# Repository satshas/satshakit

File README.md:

**IMPORTANT:** this repository is outdated, please find all the new repos about the satshakit boards here: **[satshakit Github organization](https://github.com/satshakit/)**

<h1 style="font-family: courier;" align="center"> satshakit</h1>
<p align="center">

<div align="center"><i>An improved & fabbable 100% Arduino IDE/libraries compatible board.</i></div>
</p>  

The story
--
satshakit born during my **[FabAcademy2015](http://fabacademy.org/archives/2015/eu/students/ingrassia.daniele/index.html)**  as one the first test boards for my quadcopter final project. As some of my fellow students had difficulties with **[Fabkit](http://fabacademy.org/archives/2015/doc/projects/fabkit-0.4.html)**, they tried to make this prototype board. The board was very appreciated that now almost all my fellow students made it for their exercises, or use it as a **starting point for their final projects**. Thus I decided to do this release, if anyone wants to try it. Now, one year later, I am again in a FabLab developing new satshakit boards in my spare time.

What is satshakit?
--

satshakit is a **100% Arduino IDE  and libraries compatible**, fabbable and open source board, and also an improved version of [Fabkit](http://fabacademy.org/archives/2015/doc/projects/fabkit-0.4.html). 

Main **improvements and features** over Fabkit are:

- **16Mhz** instead of 8Mhz
- **crystal** instead of resonator
- **costs less** (7-9 euro vs 13 euro)
- 100% compatible with **default Arduino IDE** (satshakit is recognized as Arduino UNO)
- ADC6/7 connected instead of ADC6/7 not connected (satshakit laser and cnc)
- larger space to easy soldering (satshakit laser and cnc)

satshakit boards
--

There are different kinds of **satshakit boards** depending on the **fabrication technique** you will use to make them, or on the **size** of the board. 

Here is a comparison table about different satshakit boards:

|name|mcu|pins|size(mm)|
| :---: | :---:|:---:|:---:|
|`satshakit laser`|ATmega328P|Arduino + ADC6/7|48 x 42|
|`satshakit cnc`|ATmega328P| Arduino + ADC6/7  |54 x 45|
|`satshakit multicore`|2 x ATmega328P| 2 x Arduino + ADC6/7|50 x 42|
|`satshakit micro`| ATmega328P|Arduino|40 x 24|

satshakit laser and cnc
--

**satshakit laser** and **satshakit cnc** are the standard versions of the satshakit. They are actually the same board, showing some layout differences to improve the fabrication process using a **fiber laser** cutter machine, or a little **cnc mill**. These satshakits are meant to be a general purpose board, having the full Arduino pinout plus ADC6/7 pins, large space for easy soldering and two led onboard for power and pin 13.

Here is the **satshakit laser board**:

And this is the **satshakit cnc board**:

**downloads (right click, download as)**

- [satshakit cnc svg](https://raw.githubusercontent.com/satshas/satshakit/master/media/satshakit_cnc/satshakit_cnc.svg)
- [satshakit cnc internal png](https://raw.githubusercontent.com/satshas/satshakit/master/media/satshakit_cnc/satshakit_cnc_internal.png)
- [satshakit cnc holes png](https://raw.githubusercontent.com/satshas/satshakit/master/media/satshakit_cnc/satshakit_cnc_holes.png)
- [satshakit cnc cut png](https://raw.githubusercontent.com/satshas/satshakit/master/media/satshakit_cnc/satshakit_cnc_cut.png)
- [satshakit cnc cut tips png](https://raw.githubusercontent.com/satshas/satshakit/master/media/satshakit_cnc/satshakit_cnc_cut_tip.png)
- [satshakit cnc schematic](https://raw.githubusercontent.com/satshas/satshakit/master/eagle_projects/satshakit_cnc/satshakit_cnc.sch)
- [satshakit cnc board](https://raw.githubusercontent.com/satshas/satshakit/master/eagle_projects/satshakit_cnc/satshakit_cnc.brd)
- [satshakit laser svg](https://raw.githubusercontent.com/satshas/satshakit/master/media/satshakit_laser/satshakit_laser.svg)
- [satshakit laser schematic](https://raw.githubusercontent.com/satshas/satshakit/master/eagle_projects/satshakit_laser/satshakit_laser.sch)
- [satshakit laser board](https://raw.githubusercontent.com/satshas/satshakit/master/eagle_projects/satshakit_laser/satshakit_laser.brd)
- [satshakit laser and cnc BOM Open Document](https://github.com/satshas/satshakit/raw/master/docs/satshakit_others/satshakit_BOM.ods)
- [satshakit laser and cnc BOM Excel](https://github.com/satshas/satshakit/raw/master/docs/satshakit_others/satshakit_BOM.xlsx)

**media**

satshakit laser:

satshakit cnc:

satshakit cnc blinks:

satshakit programmed with a FabISP:

Here are some videos of satshakit while is working with **different configuration and/or sensors**:

satshakit car with sonars sensors and Raspberry Pi:

satshakit little radar, a **satshakit modified board** with an ULN2003A:

satshakit micro
--

**satshakit micro** is a downsized version of the satshakit laser and cnc, developed to be used in **constrained space applications** like embedding the board in textiles or in small objects, or useful for who wants just a **bare metal board** to start with, also easy to be modified and/or customized. While satshakit micro is less than half the size of the other satshakits, it's a **full featured board** with the full Adruino pinout, missing only the possibility to be programmed using an FTDI cable.

Here is the **satshakit micro board**:

**downloads (right click, download as)**

- [satshakit micro svg](https://raw.githubusercontent.com/satshas/satshakit/master/media/satshakit_micro/satshakit_micro.svg)
- [satshakit micro internal png](https://raw.githubusercontent.com/satshas/satshakit/master/media/satshakit_micro/satshakit_micro_internal.png)
- [satshakit micro holes png](https://raw.githubusercontent.com/satshas/satshakit/master/media/satshakit_micro/satshakit_micro_holes.png)
- [satshakit micro cut png](https://raw.githubusercontent.com/satshas/satshakit/master/media/satshakit_micro/satshakit_micro_cut.png)
- [satshakit micro cut tips png](https://raw.githubusercontent.com/satshas/satshakit/master/media/satshakit_micro/satshakit_micro_cut_tips.png)
- [satshakit micro schematic](https://raw.githubusercontent.com/satshas/satshakit/master/eagle_projects/satshakit_micro/satshakit_micro.sch)
- [satshakit micro board](https://raw.githubusercontent.com/satshas/satshakit/master/eagle_projects/satshakit_micro/satshakit_micro.brd)
- [satshakit micro BOM Open Document](https://github.com/satshas/satshakit/raw/master/docs/satshakit_micro/satshakit_micro_BOM.ods)
- [satshakit micro BOM Excel](https://github.com/satshas/satshakit/raw/master/docs/satshakit_micro/satshakit_micro_BOM.xlsx)

**media**

satshakit micro blink:

satshakit multicore
--

**satshakit multicore** boards born as a further experiment on **MCU multithreading and networking**. satshakit multicore boards have only the following modifications in confront of the standard satshakit: 4 extra pin headers (1 GND,1 VCC,1 A4, 1 A5). These pin headers serve also a structural pillars to build a modular satshakit tower. So modular satshakit share the same power source, and can direct communicate with **I2C**. 

Here is the **satshakit multicore board**:

**downloads (right click, download as)**

- [satshakit multicore svg](https://raw.githubusercontent.com/satshas/satshakit/master/media/satshakit_multicore/satshakit_multicore.svg)
- [satshakit multicore schematic](https://raw.githubusercontent.com/satshas/satshakit/master/eagle_projects/satshakit_multicore/satshakit_multicore.sch)
- [satshakit multicore board](https://raw.githubusercontent.com/satshas/satshakit/master/eagle_projects/satshakit_multicore/satshakit_multicore.brd)
- [satshakit multicore BOM Open Document](https://github.com/satshas/satshakit/raw/master/docs/satshakit_others/satshakit_BOM.ods)
- [satshakit multicore BOM Excel](https://github.com/satshas/satshakit/raw/master/docs/satshakit_others/satshakit_BOM.xlsx)

**media**

5-core satshakit system:

satshakit multicore assembly & test:

satshakit multicore blink:

quad satshakit bluetooth triangulation:

satshakit power board
--

Due to the power requirements of a multicore satshakit system and to eventually provide power to **3.3V devices**, I have also developed a simple power board. This power board can work with 7V-12V as input voltage, and give out 5V and 3.3V. I made this power board with the components I had available, obviously you can make this board only with SMD components.

**downloads (right click, download as)**

- [satshakit power board schematic](https://raw.githubusercontent.com/satshas/satshakit/master/eagle_projects/satshakit_power_board/satshakit_power_board.sch)
- [satshakit power board board](https://raw.githubusercontent.com/satshas/satshakit/master/eagle_projects/satshakit_power_board/satshakit_power_board.brd)

Here is a picture of a soldered power board:

Getting Started
--
A satshakit board is **totally like an Arduino board**, thus is possible to use the Arduino IDE without any modification. When you finish solder satshakit, you're ready to program it. If you want to use satshakit as an Arduino, you first need to **upload Arduino bootloader**. This will also set the ATmega328P fuses as the same of an Arduino UNO.
 To do this you need to use a **programmer**, for example another Arduino or FabISP. If you plan to program a satshakit with an Arduino, be sure to upload the **Arduino as ISP skecth** before connecting the satshakit to it.

Here are the connection schemas to program **satshakit laser**, **satshakit cnc** or a **satshakit multicore** with an Arduino as ISP or with a FabISP:

If you made a **satshakit micro**, here are the connection schemas to program it as before for the other satshakits:

Once everything is connected, follow these steps to upload Arduino bootloader:

1. open Arduino IDE 
2. select proper programmer (for example Arduino as ISP or USBtinyISP) 
3. select Arduino UNO as board
4. click on tools->Burn Bootloader

If you made a satshakit cnc, satshakit laser or satshakit multicore, you can use an **FTDI USB cable to upload and use you favourite sketch** without the need to use a programmer anymore. If you made a satshakit micro, you have always to use a programmer, and use the **Sketch >Upload using a programmer** function of the Arduino IDE.

Here is the connection schema to program a satshakit using the FTDI cable:

Remember that if you don't have an FTDI cable you always need a programmer, and to select **File->Upload using a programmer** to upload the code to satshakit.

To use a satshakit like an Arduino, here is the Arduino pinout on satshakit cnc, satshakit laser and satshakit multicore:

And here is the Arduino pinout of the satshakit micro:

What's in the repo
--
- **[docs](https://github.com/satshas/satshakit/tree/master/docs)**: BOM files for Farnell
- **[egle projects](https://github.com/satshas/satshakit/tree/master/eagle_projects)**: eagle projects of satshakit
- **[media](https://github.com/satshas/satshakit/tree/master/media)**: svg of satshakits, connections schemas, images for cnc milling machine and fiber laser cutter, other images

Authors
--

**satshakit cnc and micro:**
- Daniele Ingrassia

**satshakit laser, multicore and power board:**

- Daniele Ingrassia and [Engineering Ingegneria Informatica](http://www.eng.it)

Contact
--
- **ingrassiada@gmail.com**
- **[linkedin](http://it.linkedin.com/in/danieleingrassia)**

Thanks
--
[Fablab opendot](http://www.opendotlab.it/)<br />
info@opendotlab.it<br />
Via Tertulliano N70, 20137, Milan, Italy<br />
 +39.02.36519890<br />

[Fablab Kamp-Lintfort](http://fablab.hochschule-rhein-waal.de/index.php/de/)<br />
Hochschule Rhein-Waal<br />
Friedrich-Heinrich-Allee 25, 47475 Kamp-Lintfort, Germany<br />
fablab@hochschule-rhein-waal.de

License
--
This work is licensed under the terms of Attribution-ShareAlike 4.0 International ([CC BY-NC-SA 4.0](https://creativecommons.org/licenses/by-sa/4.0/)).

Disclaimer  
--

<div class="align-justify">
This hardware/software is provided "as is", and you use the hardware/software at your own risk. Under no circumstances shall any author be liable for direct, indirect, special, incidental, or consequential damages resulting from the use, misuse, or inability to use this hardware/software, even if the authors have been advised of the possibility of such damages.</div>

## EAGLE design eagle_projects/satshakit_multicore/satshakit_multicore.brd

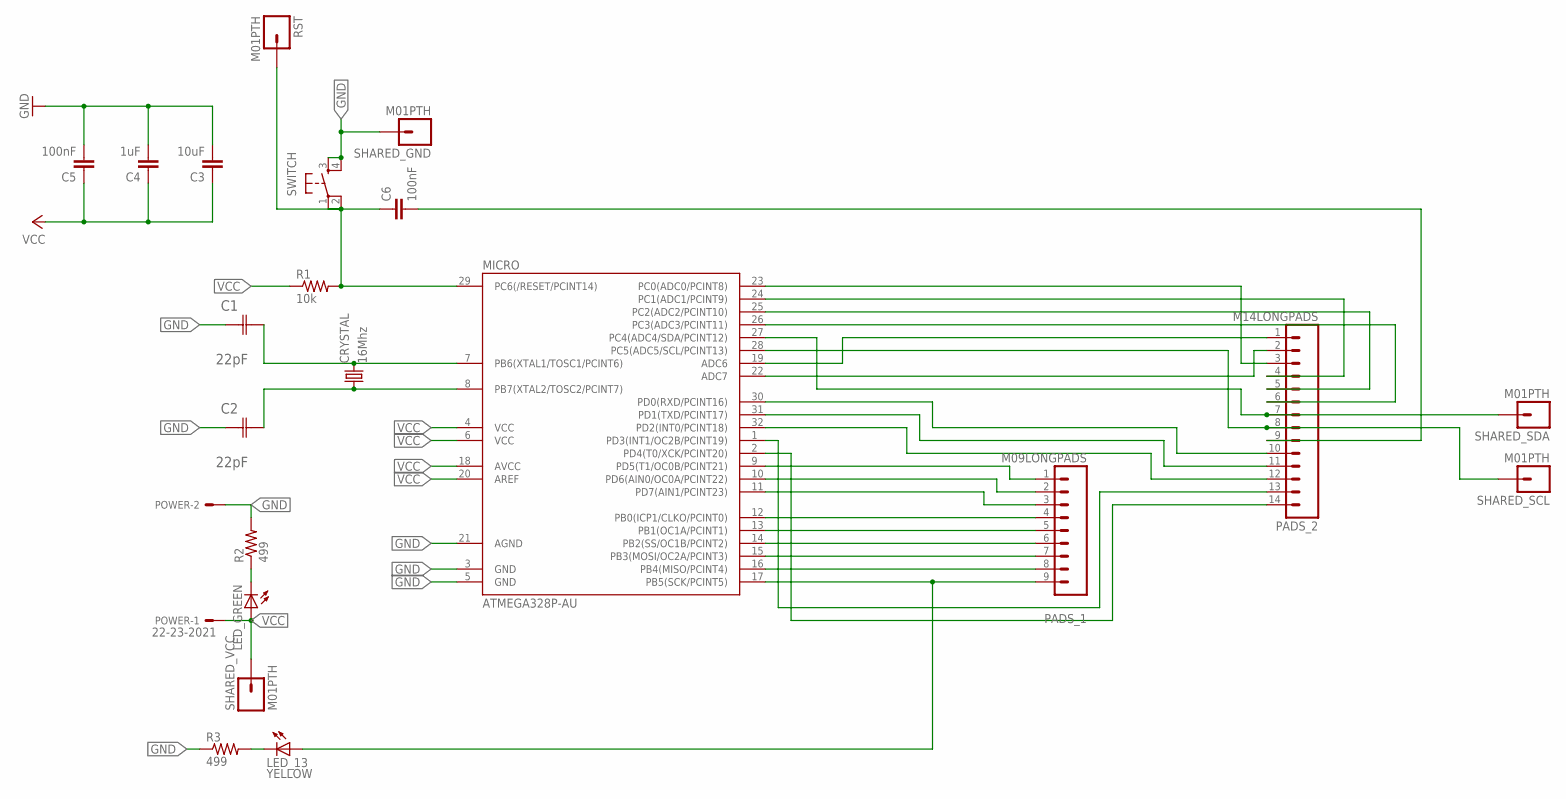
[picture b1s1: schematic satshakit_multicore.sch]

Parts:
C1, C2: 22pF; CAPC3216X178N
C3: 10uF; 1206
C4: 1uF; 1206
C5, C6: 100nF; 1206
CRYSTAL: 16Mhz; CSM-7X-DU
LED_13: YELLOW; 1206
LED_GREEN: LED1206; 1206
MICRO: ATMEGA328P-AU; TQFP32-08
PADS_1: M09LONGPADS; 1X09_LONGPADS
PADS_2: M14LONGPADS; 1X14-LONGPADS
POWER: 22-23-2021
R1: 10k; 1206
R2, R3: 499; 1206
RST: M01PTH; 1X01
SHARED_GND: M01PTH; 1X01
SHARED_SCL: M01PTH; 1X01
SHARED_SDA: M01PTH; 1X01
SHARED_VCC: M01PTH; 1X01
SWITCH: 6MM_SWITCH6MM_SWITCH; 6MM_SWITCH

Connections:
GND: C1.1 (C1), C2.1 (C1), C3.2, C4.2, C5.2, MICRO.3 (GND), MICRO.5 (GND), MICRO.21 (AGND), POWER.2, R2.2, R3.1, SHARED_GND.1, SWITCH.3 (S), SWITCH.4 (S1)
unnamed: MICRO.9 (PD5(T1/OC0B/PCINT21)), PADS_1.1
unnamed: C1.2 (C2), CRYSTAL.2, MICRO.7 (PB6(XTAL1/TOSC1/PCINT6))
unnamed: C6.2, PADS_2.9
unnamed: MICRO.10 (PD6(AIN0/OC0A/PCINT22)), PADS_1.2
unnamed: MICRO.11 (PD7(AIN1/PCINT23)), PADS_1.3
unnamed: MICRO.12 (PB0(ICP1/CLKO/PCINT0)), PADS_1.4
unnamed: MICRO.13 (PB1(OC1A/PCINT1)), PADS_1.5
unnamed: MICRO.14 (PB2(SS/OC1B/PCINT2)), PADS_1.6
unnamed: C2.2 (C2), CRYSTAL.1, MICRO.8 (PB7(XTAL2/TOSC2/PCINT7))
unnamed: MICRO.15 (PB3(MOSI/OC2A/PCINT3)), PADS_1.7
unnamed: MICRO.16 (PB4(MISO/PCINT4)), PADS_1.8
unnamed: LED_13.1 (A), MICRO.17 (PB5(SCK/PCINT5)), PADS_1.9
unnamed: MICRO.19 (ADC6), PADS_2.1
unnamed: MICRO.22 (ADC7), PADS_2.2
unnamed: MICRO.23 (PC0(ADC0/PCINT8)), PADS_2.3
unnamed: MICRO.24 (PC1(ADC1/PCINT9)), PADS_2.4
unnamed: MICRO.25 (PC2(ADC2/PCINT10)), PADS_2.5
unnamed: MICRO.26 (PC3(ADC3/PCINT11)), PADS_2.6
unnamed: MICRO.27 (PC4(ADC4/SDA/PCINT12)), PADS_2.7, SHARED_SDA.1
unnamed: MICRO.30 (PD0(RXD/PCINT16)), PADS_2.10
unnamed: MICRO.31 (PD1(TXD/PCINT17)), PADS_2.11
unnamed: MICRO.32 (PD2(INT0/PCINT18)), PADS_2.12
unnamed: MICRO.1 (PD3(INT1/OC2B/PCINT19)), PADS_2.13
unnamed: MICRO.2 (PD4(T0/XCK/PCINT20)), PADS_2.14
unnamed: MICRO.28 (PC5(ADC5/SCL/PCINT13)), PADS_2.8, SHARED_SCL.1
unnamed: LED_GREEN.2 (C), R2.1
unnamed: LED_13.2 (C), R3.2
unnamed: C6.1, MICRO.29 (PC6(/RESET/PCINT14)), R1.2, RST.1, SWITCH.1, SWITCH.2 (P1)
VCC: C3.1, C4.1, C5.1, LED_GREEN.1 (A), MICRO.4 (VCC), MICRO.6 (VCC), MICRO.18 (AVCC), MICRO.20 (AREF), POWER.1, R1.1, SHARED_VCC.1

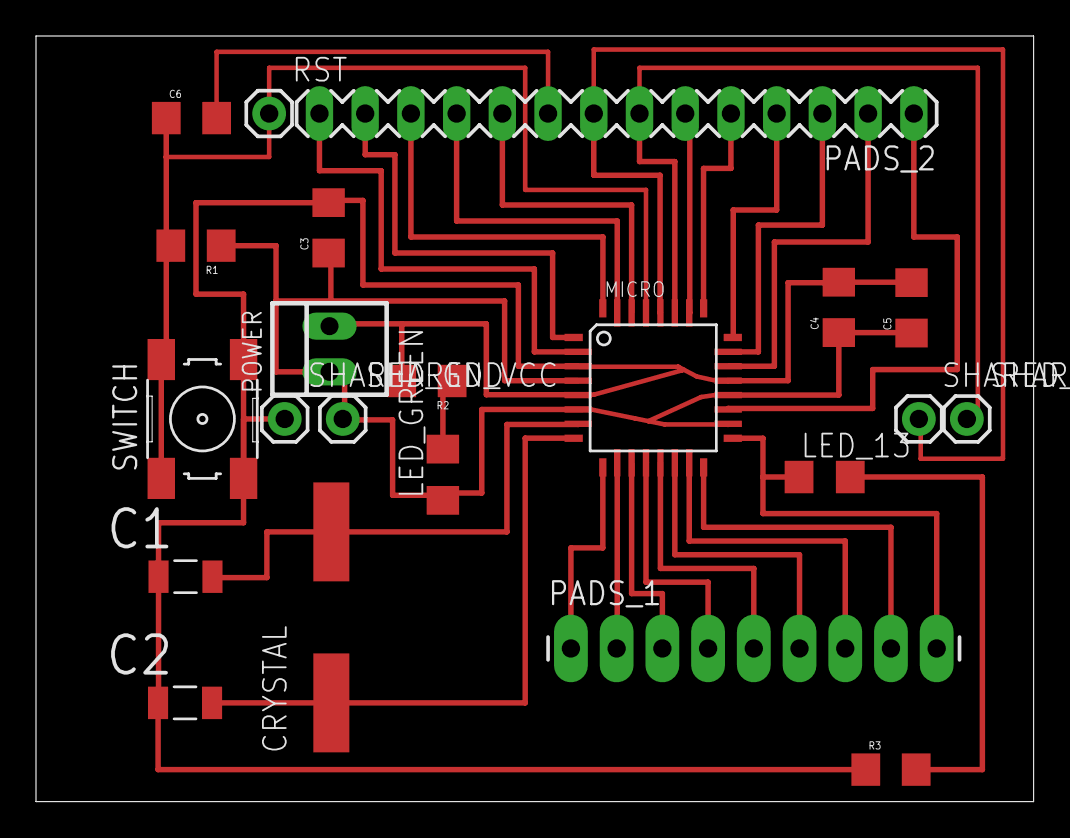
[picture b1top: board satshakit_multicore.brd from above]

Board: 2 copper layers, 55.4 x 42.5 mm, 22 parts (0 on the bottom side), 30 nets.

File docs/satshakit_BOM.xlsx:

Eagle Part | Value | Manufacturer Part No | Package | Description | FARNELL | Price € | Quantity | Min. Quantity Cost €
MICRO | - | ATMEGA328P-AU | TQFP-32 | microcontroller | 1715486 | 2.78 | 1.0 | 2.78
CRYSTAL | 16Mhz/18pF | MCRSD16000F183000RR | SMD 11.4 x 4.7 mm | crystal | 2395958 | 0.2 | 1.0 | 0.2
LED_GREEN | green | MCL-S250GC | 1206.0 | green led | 1581232 | 0.12 | 1.0 | 0.6
LED_YELLOW | yellow | MCL-S250YC | 1206.0 | yellow led | 1581231 | 0.05 | 1.0 | 0.26
SWITCH | - | B3SN-3112P | 6 x 6 x 3.1 mm | switch | 2076274 | 0.65 | 1.0 | 0.65
R1 | 10K | ERJ8GEYJ103V | 1206.0 | resistor | 2057856 | 0.026 | 1.0 | 0.26
R2/R3 | 499.0 | CRCW1206499RFKEA | 1206.0 | resistor | 1470020 | 0.028 | 2.0 | 0.28
C1/C2 | 22pF | MC1206N220J500CT | 1206.0 | capacitor | 2320891 | 0.047 | 2.0 | 0.47
C3 | 10uF | MC1206X106K250CT | 1206.0 | capacitor | 2112753 | 0.154 | 1.0 | 0.154
C4 | 1uF | MC1206F105Z500CT | 1206.0 | capacitor | 1759455 | 0.0634 | 1.0 | 0.634
C5/C6 | 100nF | MC1206B104K500CT | 1206.0 | capacitor | 1759361 | 0.0354 | 2.0 | 0.35
PAD_1/PAD_2 | - | 6.1304011021E10 | 2.54 mm | pin header | 2356192 | 1.77 | 1.0 | 1.77
POWER/PAD_B | - | M20-9990246 | 2.54 mm | pin header | 1022247 | 0.0653 | 1.0 | 0.65
 |  |  |  |  |  |  |  | Total cost
 |  |  |  |  |  |  |  | 9.06

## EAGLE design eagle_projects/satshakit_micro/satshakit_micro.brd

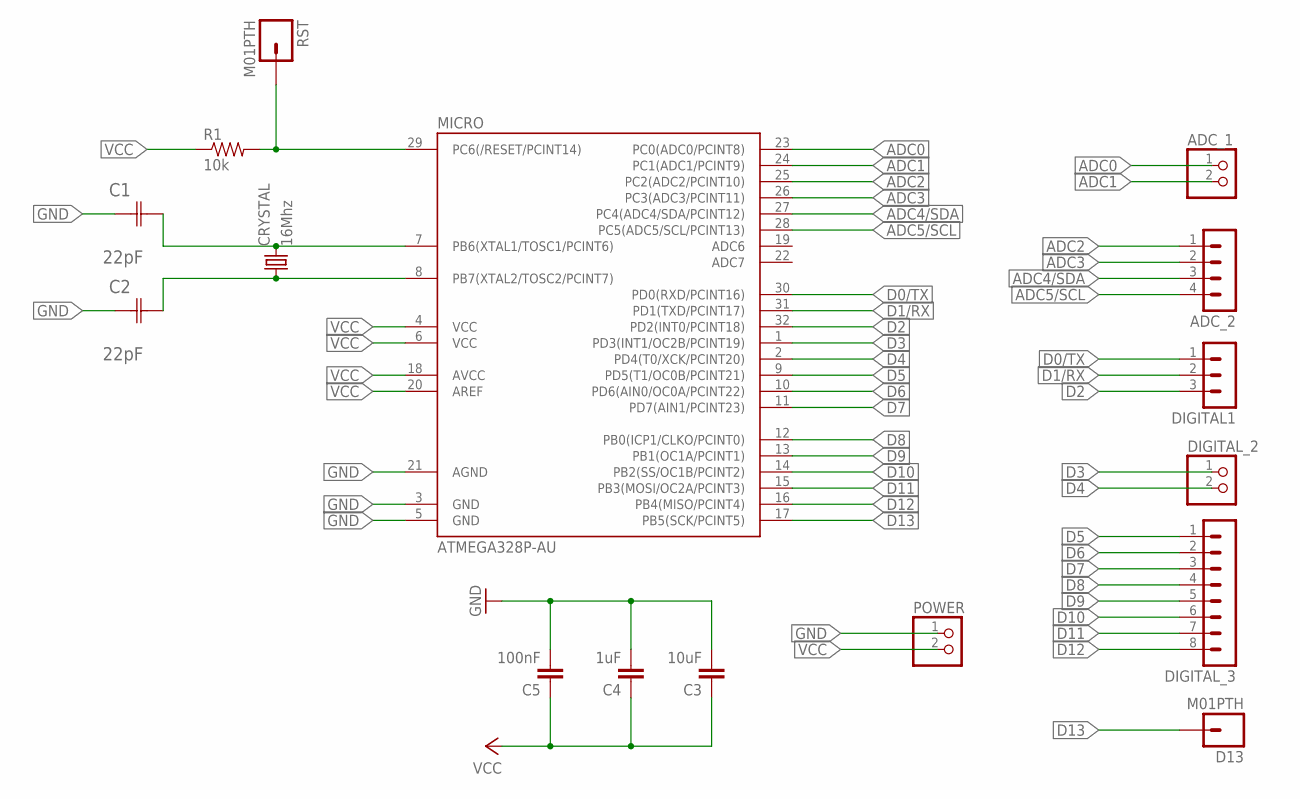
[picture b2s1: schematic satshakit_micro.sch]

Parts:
ADC_1: PINHD-1X2; 1X02
ADC_2: MA04-1
C1, C2: 22pF; CAPC3216X178N
C3: 10uF; 1206
C4: 1uF; 1206
C5: 100nF; 1206
CRYSTAL: 16Mhz; CSM-7X-DU
D13: M01PTH; 1X01
DIGITAL1: MA03-1
DIGITAL_2: PINHD-1X2; 1X02
DIGITAL_3: MA08-1
MICRO: ATMEGA328P-AU; TQFP32-08
POWER: PINHD-1X2; 1X02
R1: 10k; 1206
RST: M01PTH; 1X01

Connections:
ADC0: ADC_1.1, MICRO.23 (PC0(ADC0/PCINT8))
ADC1: ADC_1.2, MICRO.24 (PC1(ADC1/PCINT9))
ADC2: ADC_2.1, MICRO.25 (PC2(ADC2/PCINT10))
ADC3: ADC_2.2, MICRO.26 (PC3(ADC3/PCINT11))
ADC4/SDA: ADC_2.3, MICRO.27 (PC4(ADC4/SDA/PCINT12))
ADC5/SCL: ADC_2.4, MICRO.28 (PC5(ADC5/SCL/PCINT13))
D0/TX: DIGITAL1.1, MICRO.30 (PD0(RXD/PCINT16))
D1/RX: DIGITAL1.2, MICRO.31 (PD1(TXD/PCINT17))
D2: DIGITAL1.3, MICRO.32 (PD2(INT0/PCINT18))
D3: DIGITAL_2.1, MICRO.1 (PD3(INT1/OC2B/PCINT19))
D4: DIGITAL_2.2, MICRO.2 (PD4(T0/XCK/PCINT20))
D5: DIGITAL_3.1, MICRO.9 (PD5(T1/OC0B/PCINT21))
D6: DIGITAL_3.2, MICRO.10 (PD6(AIN0/OC0A/PCINT22))
D7: DIGITAL_3.3, MICRO.11 (PD7(AIN1/PCINT23))
D8: DIGITAL_3.4, MICRO.12 (PB0(ICP1/CLKO/PCINT0))
D9: DIGITAL_3.5, MICRO.13 (PB1(OC1A/PCINT1))
D10: DIGITAL_3.6, MICRO.14 (PB2(SS/OC1B/PCINT2))
D11: DIGITAL_3.7, MICRO.15 (PB3(MOSI/OC2A/PCINT3))
D12: DIGITAL_3.8, MICRO.16 (PB4(MISO/PCINT4))
D13: D13.1, MICRO.17 (PB5(SCK/PCINT5))
GND: C1.1 (C1), C2.1 (C1), C3.2, C4.2, C5.2, MICRO.3 (GND), MICRO.5 (GND), MICRO.21 (AGND), POWER.1
unnamed: C1.2 (C2), CRYSTAL.2, MICRO.7 (PB6(XTAL1/TOSC1/PCINT6))
unnamed: MICRO.29 (PC6(/RESET/PCINT14)), R1.2, RST.1
unnamed: C2.2 (C2), CRYSTAL.1, MICRO.8 (PB7(XTAL2/TOSC2/PCINT7))
VCC: C3.1, C4.1, C5.1, MICRO.4 (VCC), MICRO.6 (VCC), MICRO.18 (AVCC), MICRO.20 (AREF), POWER.2, R1.1

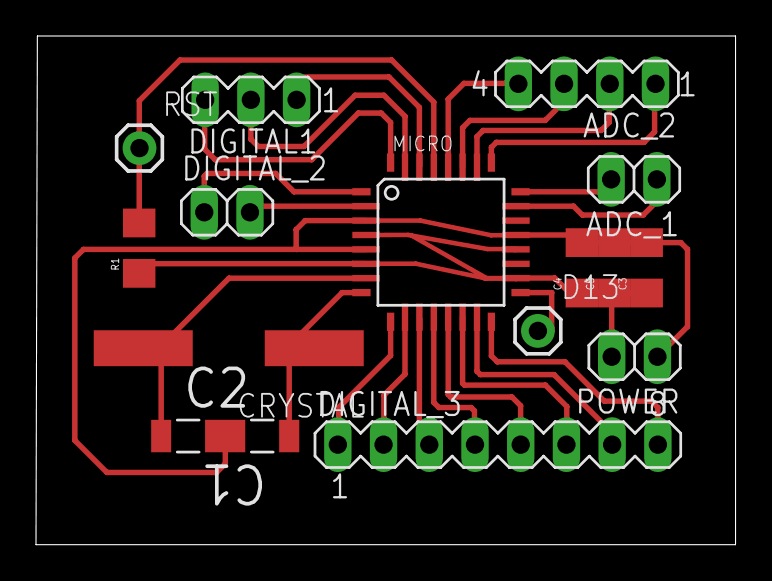
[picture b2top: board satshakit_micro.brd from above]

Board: 2 copper layers, 38.9 x 28.3 mm, 16 parts (0 on the bottom side), 25 nets.

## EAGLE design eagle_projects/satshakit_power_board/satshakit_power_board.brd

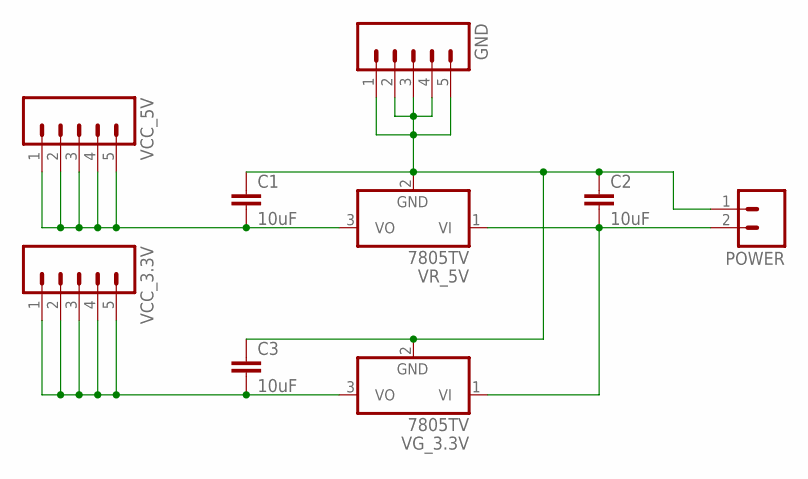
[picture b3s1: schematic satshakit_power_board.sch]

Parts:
C1, C2, C3: 10uF; 1206
GND: M05PTH_LONGPADS; 1X05_LONGPADS
POWER: M02; 1X02_LONGPADS
VCC_3.3V, VCC_5V: M05PTH_LONGPADS; 1X05_LONGPADS
VG_3.3V: 7805TV; TO220V
VR_5V: 7805TV; TO220V

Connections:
unnamed: C3.2, VCC_3.3V.1, VCC_3.3V.2, VCC_3.3V.3, VCC_3.3V.4, VCC_3.3V.5, VG_3.3V.3 (VO)
unnamed: C1.2, VCC_5V.1, VCC_5V.2, VCC_5V.3, VCC_5V.4, VCC_5V.5, VR_5V.3 (VO)
unnamed: C2.2, POWER.2, VG_3.3V.1 (VI), VR_5V.1 (VI)
unnamed: C1.1, C2.1, C3.1, GND.1, GND.2, GND.3, GND.4, GND.5, POWER.1, VG_3.3V.2 (GND), VR_5V.2 (GND)

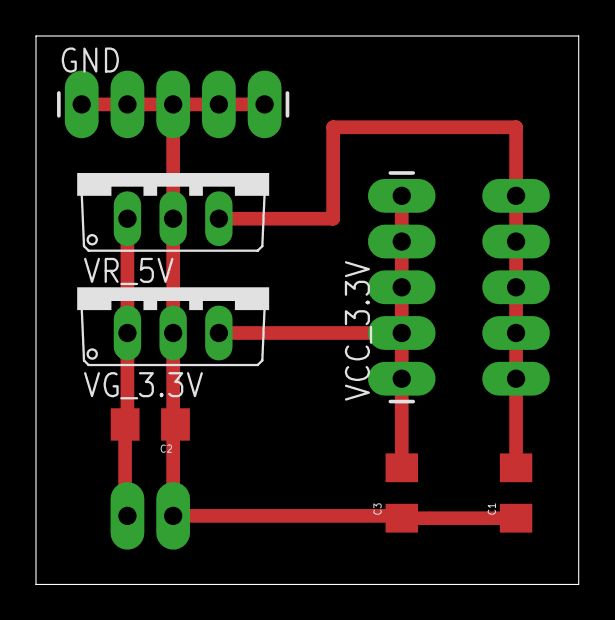
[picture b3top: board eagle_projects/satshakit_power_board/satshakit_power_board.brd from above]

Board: 2 copper layers, 30.2 x 30.5 mm, 9 parts (1 on the bottom side), 4 nets.

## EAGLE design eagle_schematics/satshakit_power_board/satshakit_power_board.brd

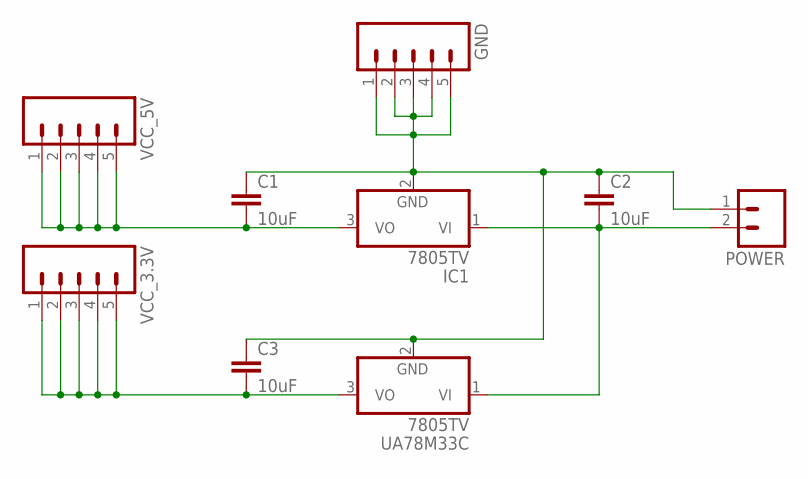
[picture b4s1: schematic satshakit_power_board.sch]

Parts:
C1, C2, C3: 10uF; 1206
GND: M05PTH_LONGPADS; 1X05_LONGPADS
IC1: 7805TV; TO220V
POWER: M02; 1X02_LONGPADS
UA78M33C: 7805TV; TO220V
VCC_3.3V, VCC_5V: M05PTH_LONGPADS; 1X05_LONGPADS

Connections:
unnamed: C3.2, UA78M33C.3 (VO), VCC_3.3V.1, VCC_3.3V.2, VCC_3.3V.3, VCC_3.3V.4, VCC_3.3V.5
unnamed: C1.2, IC1.3 (VO), VCC_5V.1, VCC_5V.2, VCC_5V.3, VCC_5V.4, VCC_5V.5
unnamed: C2.2, IC1.1 (VI), POWER.2, UA78M33C.1 (VI)
unnamed: C1.1, C2.1, C3.1, GND.1, GND.2, GND.3, GND.4, GND.5, IC1.2 (GND), POWER.1, UA78M33C.2 (GND)

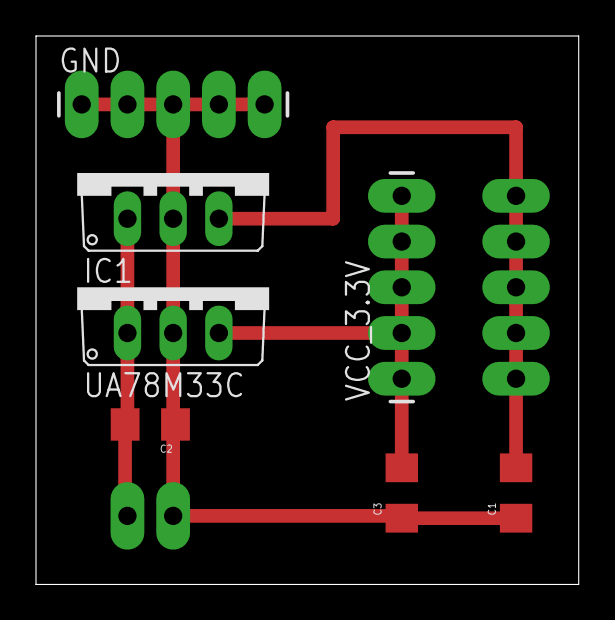
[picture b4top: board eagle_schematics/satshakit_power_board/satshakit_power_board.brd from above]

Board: 2 copper layers, 30.2 x 30.5 mm, 9 parts (1 on the bottom side), 4 nets.

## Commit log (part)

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2015-04-14 first satshakit commit
2015-04-14 readme fix
2015-04-15 added satshakit video
2015-04-19 v0.2 programming from FTDI cable
2015-04-20 fixed a little error on the board
2015-04-20 updated imgs
2015-04-21 minor fixes
2015-04-21 fixed fabkit link
2015-04-24 added new videos
2015-04-27 added led matrix video
2015-05-06 added satshakit modular and power board
2015-05-06 added modular imgs
2015-05-07 added thanks
2015-07-22 license change
2016-03-17 added Engineering as author
2016-05-07 added satshakit micro and cnc versions, reoganized the readme file
2016-05-07 readme fixes
2016-05-17 added right click download as writings
2017-01-22 added the link to satshakit organization

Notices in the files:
parts and their libraries:
01_SparkFun: Licensing: CC v3.0 Share-Alike You are welcome to use this library for commercial purposes.
